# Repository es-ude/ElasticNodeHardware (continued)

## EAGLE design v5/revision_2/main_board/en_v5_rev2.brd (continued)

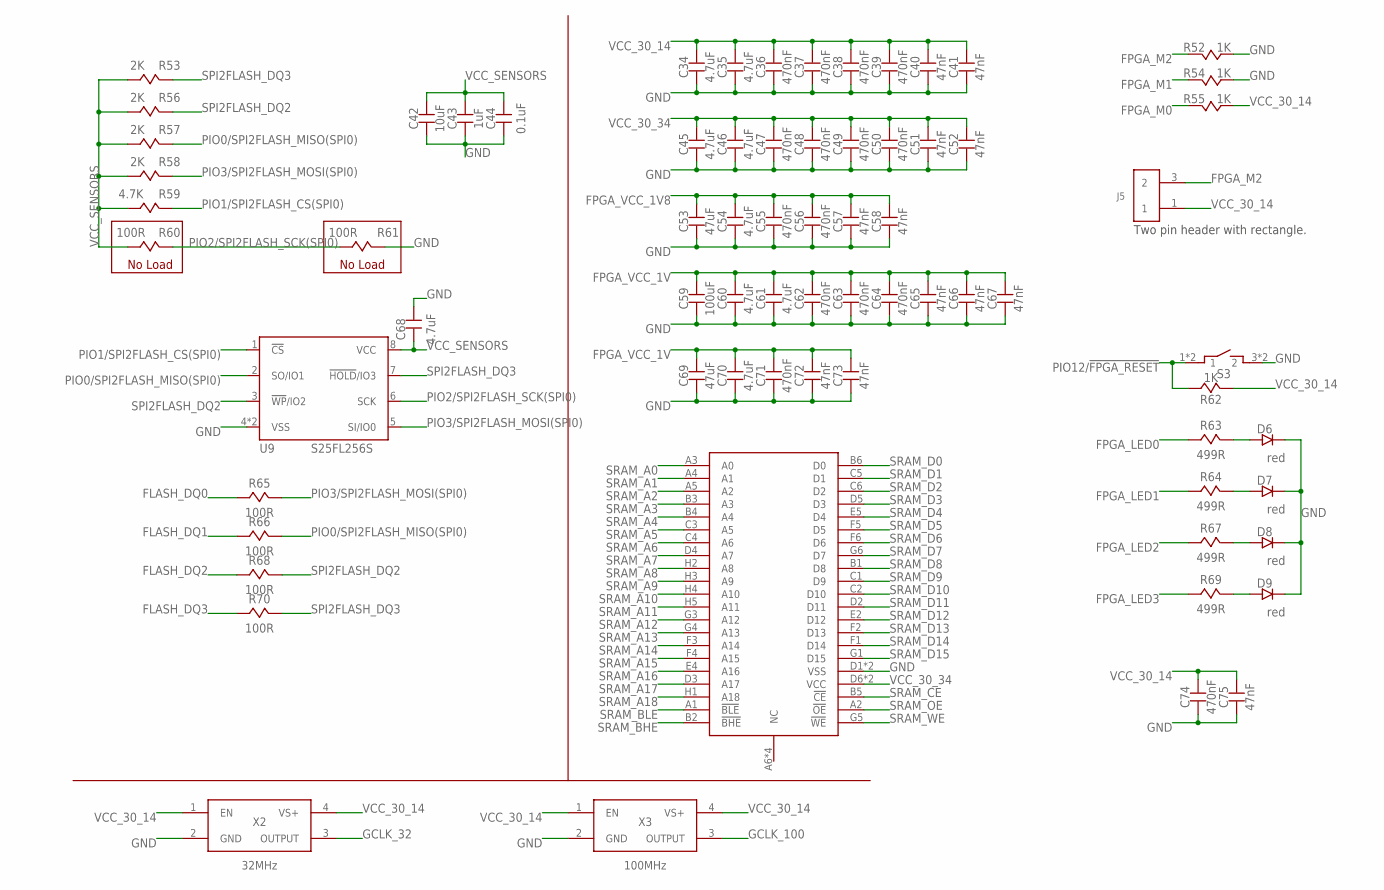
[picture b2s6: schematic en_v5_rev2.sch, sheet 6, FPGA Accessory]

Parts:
C34, C35, C45, C46, C54, C60, C61, C68, C70: 4.7uF; CAPC1608-0603
C36, C37, C38, C39, C47, C48, C49, C50, C55, C56, C62, C63, C64, C71, C74: 470nF; 0402
C40, C41, C51, C52, C57, C58, C65, C66, C67, C72, C73, C75: 47nF; 0402
C42: 10uF; CAPC1608-0603
C43: 1uF; 0402
C44: 0.1uF; 0402
C53, C69: 47uF; 0805
C59: 100uF; 0805
D6, D7, D8, D9: red; 0402
J5: FEMALE_HEADER_2X1; 2X1_HEADER
R52, R54, R55, R62: 1K; 0402
R53, R56, R57, R58: 2K; 0402
R59: 4.7K; 0402
R60, R61, R65, R66, R68, R70: 100R; 0402
R63, R64, R67, R69: 499R; 0402
S3: TACTILE-SWITCH
U9: S25FL256S; WSON6X8MM
U10: CY7C1051DV33; BGA-48
X2: 32MHz; 3.2X2.5_OSC
X3: 100MHz; 3.2X2.5_OSC

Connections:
FLASH_DQ0: R65.1; also elsewhere on the board
FLASH_DQ1: R66.1; also elsewhere on the board
FLASH_DQ2: R68.1; also elsewhere on the board
FLASH_DQ3: R70.1; also elsewhere on the board
FPGA_LED0: R63.1; also elsewhere on the board
FPGA_LED1: R64.1; also elsewhere on the board
FPGA_LED2: R67.1; also elsewhere on the board
FPGA_LED3: R69.1; also elsewhere on the board
FPGA_M0: R55.2; also elsewhere on the board
FPGA_M1: R54.2; also elsewhere on the board
FPGA_M2: J5.3 (2), R52.2; also elsewhere on the board
FPGA_VCC_1V: C59.2, C60.2, C61.2, C62.2, C63.2, C64.2, C65.2, C66.2, C67.2, C69.2, C70.2, C71.2, C72.2, C73.2; also elsewhere on the board
FPGA_VCC_1V8: C53.2, C54.2, C55.2, C56.2, C57.2, C58.2; also elsewhere on the board
GCLK_32: X2.3 (OUTPUT); also elsewhere on the board
GCLK_100: X3.3 (OUTPUT); also elsewhere on the board
GND: C34.1, C35.1, C36.1, C37.1, C38.1, C39.1, C40.1, C41.1, C42.1, C43.1, C44.1, C45.1, C46.1, C47.1, C48.1, C49.1, C50.1, C51.1, C52.1, C53.1, C54.1, C55.1, C56.1, C57.1, C58.1, C59.1, C60.1, C61.1, C62.1, C63.1, C64.1, C65.1, C66.1, C67.1, C68.2, C69.1, C70.1, C71.1, C72.1, C73.1, C74.1, C75.1, D6.2, D7.2, D8.2, D9.2, R52.1, R54.1, R61.2, S3.3 (2), S3.4 (2), U9.4 (VSS), U9.9 (VSS), U10.D1 (VSS), U10.E6 (VSS), X2.2 (GND), X3.2 (GND); also elsewhere on the board
unnamed: D6.1, R63.2
unnamed: D7.1, R64.2
unnamed: D8.1, R67.2
unnamed: D9.1, R69.2
PIO0/SPI2FLASH_MISO(SPI0): R57.2, R66.2, U9.2 (SO/IO1); also elsewhere on the board
PIO1/SPI2FLASH_CS(SPI0): R59.2, U9.1 (!CS); also elsewhere on the board
PIO2/SPI2FLASH_SCK(SPI0): R60.2, R61.1, U9.6 (SCK); also elsewhere on the board
PIO3/SPI2FLASH_MOSI(SPI0): R58.2, R65.2, U9.5 (SI/IO0); also elsewhere on the board
PIO12/!FPGA_RESET: R62.1, S3.1, S3.2 (1); also elsewhere on the board
SPI2FLASH_DQ2: R56.2, R68.2, U9.3 (!WP!/IO2)
SPI2FLASH_DQ3: R53.2, R70.2, U9.7 (!HOLD!/IO3)
SRAM_A0: U10.A3 (A0); also elsewhere on the board
SRAM_A1: U10.A4 (A1); also elsewhere on the board
SRAM_A2: U10.A5 (A2); also elsewhere on the board
SRAM_A3: U10.B3 (A3); also elsewhere on the board
SRAM_A4: U10.B4 (A4); also elsewhere on the board
SRAM_A5: U10.C3 (A5); also elsewhere on the board
SRAM_A6: U10.C4 (A6); also elsewhere on the board
SRAM_A7: U10.D4 (A7); also elsewhere on the board
SRAM_A8: U10.H2 (A8); also elsewhere on the board
SRAM_A9: U10.H3 (A9); also elsewhere on the board
SRAM_A10: U10.H4 (A10); also elsewhere on the board
SRAM_A11: U10.H5 (A11); also elsewhere on the board
SRAM_A12: U10.G3 (A12); also elsewhere on the board
SRAM_A13: U10.G4 (A13); also elsewhere on the board
SRAM_A14: U10.F3 (A14); also elsewhere on the board
SRAM_A15: U10.F4 (A15); also elsewhere on the board
SRAM_A16: U10.E4 (A16); also elsewhere on the board
SRAM_A17: U10.D3 (A17); also elsewhere on the board
SRAM_A18: U10.H1 (A18); also elsewhere on the board
SRAM_BHE: U10.B2 (!BHE); also elsewhere on the board
SRAM_BLE: U10.A1 (!BLE); also elsewhere on the board
SRAM_CE: U10.B5 (!CE); also elsewhere on the board
SRAM_D0: U10.B6 (D0); also elsewhere on the board
SRAM_D1: U10.C5 (D1); also elsewhere on the board
SRAM_D2: U10.C6 (D2); also elsewhere on the board
SRAM_D3: U10.D5 (D3); also elsewhere on the board
SRAM_D4: U10.E5 (D4); also elsewhere on the board
SRAM_D5: U10.F5 (D5); also elsewhere on the board
SRAM_D6: U10.F6 (D6); also elsewhere on the board
SRAM_D7: U10.G6 (D7); also elsewhere on the board
SRAM_D8: U10.B1 (D8); also elsewhere on the board
SRAM_D9: U10.C1 (D9); also elsewhere on the board
SRAM_D10: U10.C2 (D10); also elsewhere on the board
SRAM_D11: U10.D2 (D11); also elsewhere on the board
SRAM_D12: U10.E2 (D12); also elsewhere on the board
SRAM_D13: U10.F2 (D13); also elsewhere on the board
SRAM_D14: U10.F1 (D14); also elsewhere on the board
SRAM_D15: U10.G1 (D15); also elsewhere on the board
SRAM_OE: U10.A2 (!OE); also elsewhere on the board
SRAM_WE: U10.G5 (!WE); also elsewhere on the board
VCC_30_14: C34.2, C35.2, C36.2, C37.2, C38.2, C39.2, C40.2, C41.2, C74.2, C75.2, J5.1, R55.1, R62.2, X2.1 (EN), X2.4 (VS+), X3.1 (EN), X3.4 (VS+); also elsewhere on the board
VCC_30_34: C45.2, C46.2, C47.2, C48.2, C49.2, C50.2, C51.2, C52.2, U10.D6 (VCC), U10.E1 (VCC); also elsewhere on the board
VCC_SENSORS: C42.2, C43.2, C44.2, C68.1, R53.1, R56.1, R57.1, R58.1, R59.1, R60.1, U9.8 (VCC); also elsewhere on the board

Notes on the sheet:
No Load
Two pin header with rectangle.

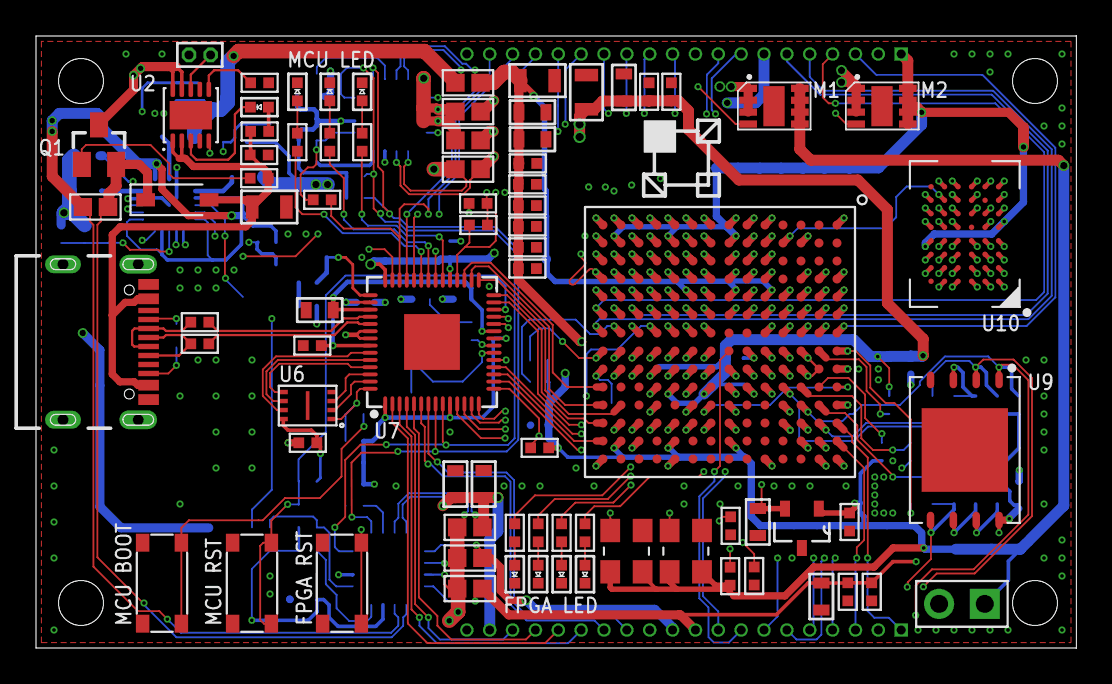
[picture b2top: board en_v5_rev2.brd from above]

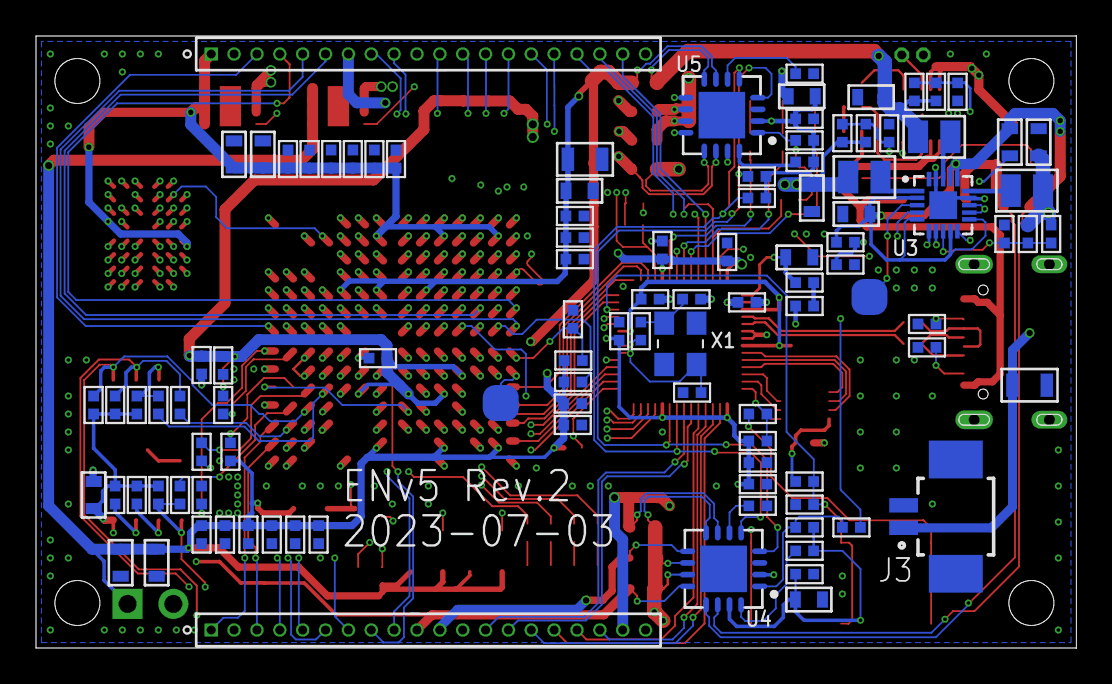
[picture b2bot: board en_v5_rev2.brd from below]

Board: 4 copper layers, 57.8 x 34.0 mm, 183 parts (104 on the bottom side), 170 nets.

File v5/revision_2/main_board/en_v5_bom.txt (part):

Qty Value                   Device                     Package                   Parts                                                                     Description                                                                                                                           
14  0.1uF                   CAPACITOR0402              0402                      C3, C14, C16, C18, C19, C20, C21, C22, C23, C24, C26, C27, C30, C44                                                                                                                                             
2   0.1uF                   CAPACITOR0603              CAPC1608-0603             C5, C6                                                                                                                                                                                                          
1   0.1uF                   CAPACITOR0805              0805                      C1                                                                                                                                                                                                              
8   0.82R                   RESISTOR0603               0603                      R16, R17, R18, R19, R20, R21, R26, R28                                                                                                                                                                          
7   0R                      RESISTORSMD_0402           0402                      R4, R10, R27, R29, R47, R48, R49                                                                                                                                                                                
1   1.5uH(MLP2016H1R5MT0S1) INDUCTORDFE201612E-R33M=P2 INDC2016X120N             L1                                                                                                                                                                                                              
1   100MHz                  OSCILLATOR3.2X2.5          3.2X2.5_OSC               X3                                                                                                                                                                                                              
7   100R                    RESISTORSMD_0402           0402                      R33, R60, R61, R65, R66, R68, R70                                                                                                                                                                               
1   100uF                   CAPACITOR0805              0805                      C59                                                                                                                                                                                                             
7   10K                     RESISTORSMD_0402           0402                      R3, R22, R23, R24, R25, R34, R44                                                                                                                                                                                
5   10uF                    CAPACITOR0603              CAPC1608-0603             C4, C8, C10, C12, C42                                                                                                                                                                                           
1   10uF                    CAPACITOR0805              0805                      C2                                                                                                                                                                                                              
3   120K                    RESISTORSMD_0402           0402                      R9, R12, R13                                                                                                                                                                                                    
1   12MHz                   QUARTZ                     3.2X2.5_OSC               X1                                                                                                                                                                                                              
1   150K                    RESISTORSMD_0402           0402                      R11                                                                                                                                                                                                             
1   180K                    RESISTORSMD_0402           0402                      R14                                                                                                                                                                                                             
7   1K                      RESISTORSMD_0402           0402                      R6, R46, R51, R52, R54, R55, R62                                                                                                                                                                                
1   1R                      RESISTORSMD_0402           0402                      R41                                                                                                                                                                                                             
2   1uF                     CAPACITOR0402              0402                      C33, C43                                                                                                                                                                                                        
1   2.2uH(MLP2016H2R2MT0S1) INDUCTORDFE201612E-R33M=P2 INDC2016X120N             L3                                                                                                                                                                                                              
1   2.7pF                   CAPACITOR0402              0402                      C11                                                                                                                                                                                                             
1   200R                    RESISTORSMD_0402           0402                      R37                                                                                                                                                                                                             
2   20pF                    CAPACITOR0402              0402                      C31, C32                                                                                                                                                                                                        
2   27R                     RESISTORSMD_0402           0402                      R42, R43                                                                                                                                                                                                        
7   2K                      RESISTORSMD_0402           0402                      R5, R45, R50, R53, R56, R57, R58                                                                                                                                                                                
1   3.3pF                   CAPACITOR0402              0402                      C9                                                                                                                                                                                                              
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
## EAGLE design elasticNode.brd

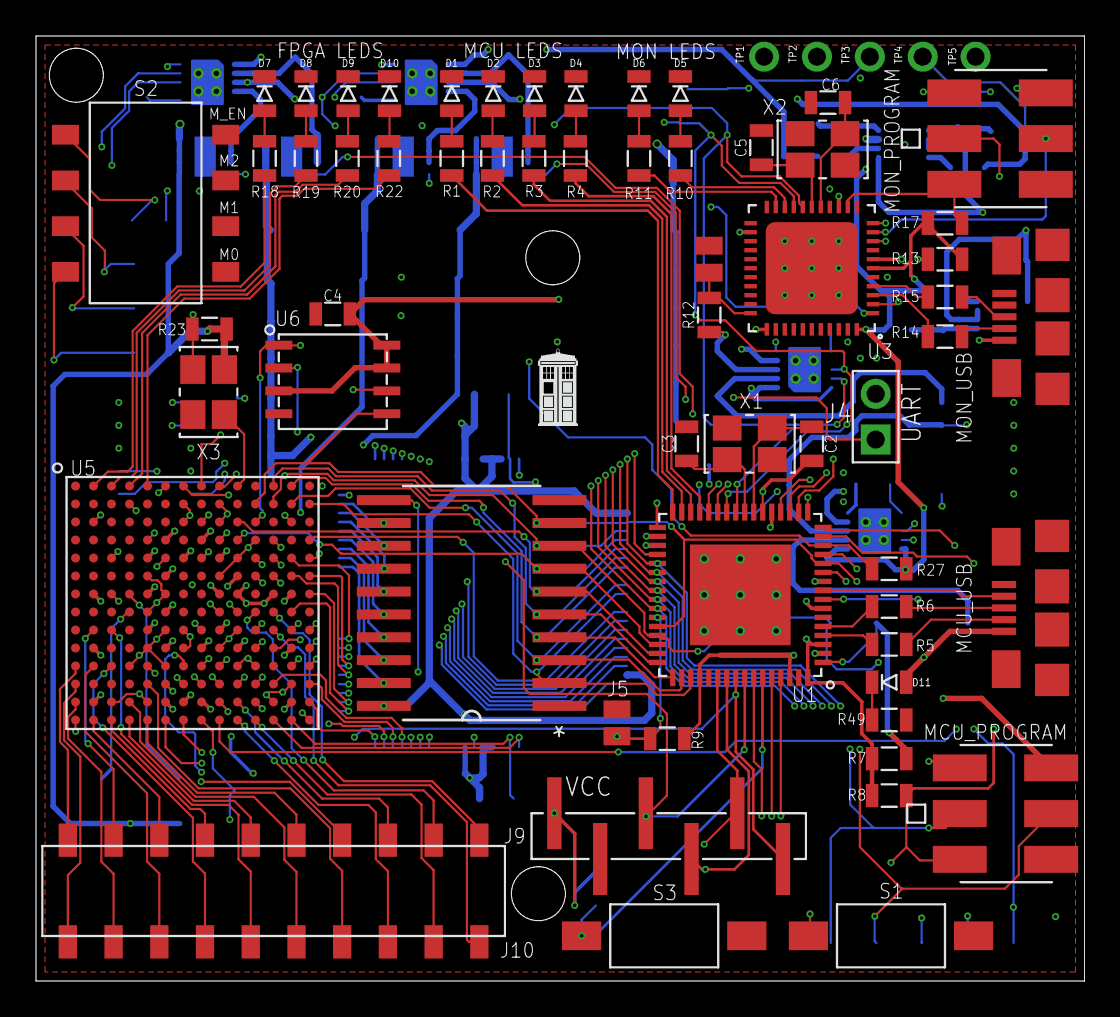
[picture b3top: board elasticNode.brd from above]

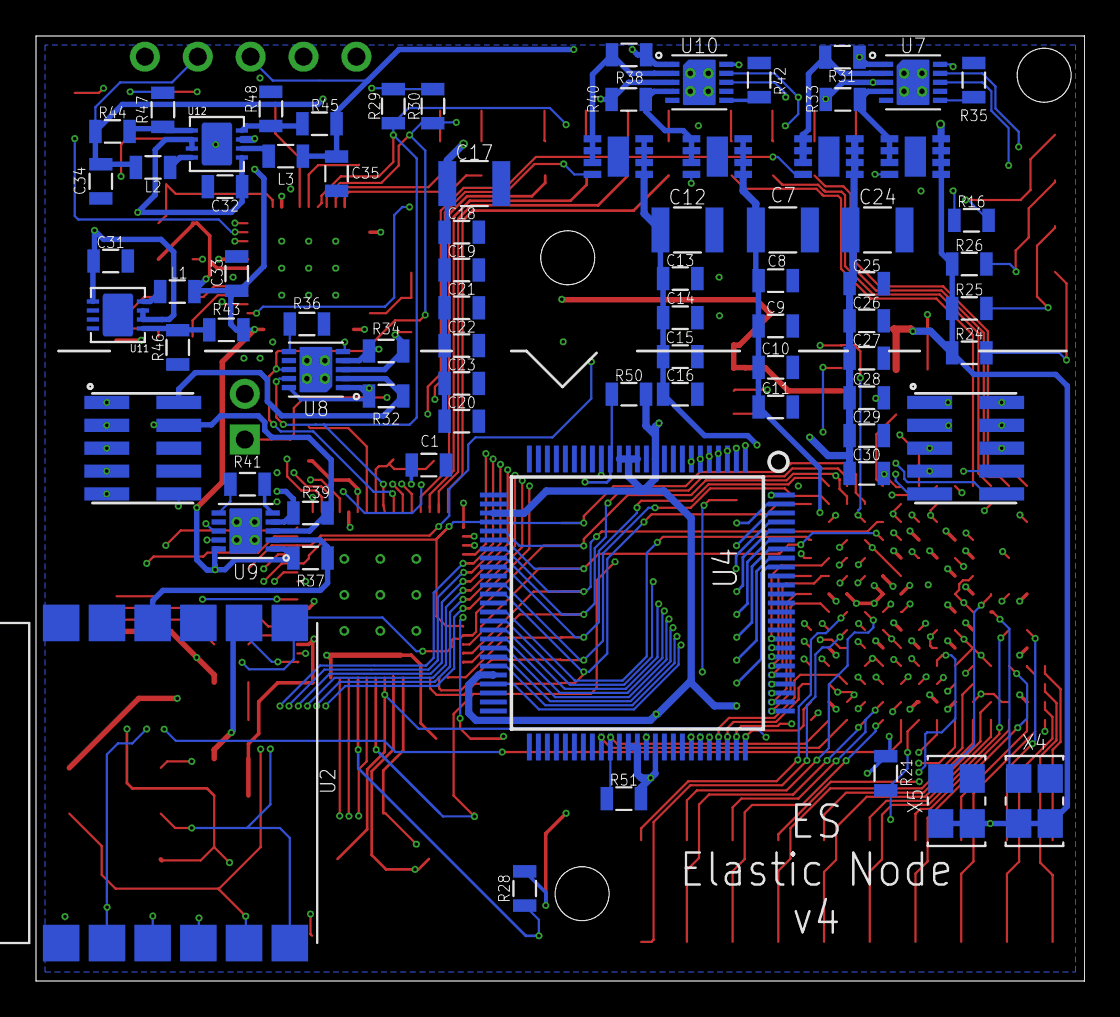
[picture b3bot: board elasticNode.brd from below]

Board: 4 copper layers, 58.2 x 52.5 mm, 141 parts (77 on the bottom side), 171 nets.

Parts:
C1, C4, C31, C32: 10u; 0805
C2, C3, C5, C6: 20p; 0805
C7, C17, C24: 100u; 1210
C8, C9, C13, C18, C19, C20, C25, C26, C27: 4.7u; 0805
C10, C11, C14, C15, C16, C21, C22, C23, C28, C29, C30: 0.47u; 0805
C12: 47u; 1210
C33, C34, C35: 22u; 0805
D1, D2, D3, D4, D5, D6: GREEN 2.2V; 0805
D7: RED 1.8V 2mA; 0805
D8, D9, D10, D11: RED; 0805
J1, J2: FEMALE_HEADER_5X2; 5X2_HEADER_SMT_1.27
J3, J6: ISP_CONN_6PIN; ICSP_SMT
J4: FEMALE_HEADER_2X1; 2X1_HEADER
J5, J7: JUMPER; JUMPER_SMT
J8, J11: USB_CONNMICRO_SMT; USB_MICRO_B_SMT
J9: JTAG_CONN_6PINSMT; 6X1_JTAG
J10: FEMALE_HEADER_10X2; 10X2_HEADER_SMT
L1, L2, L3: 3.3uH; 0805
M1, M2, M3, M4: SISS23DN; POWERPAK1212-8
R1, R2, R3, R4, R10, R11: 550; 0805
R5, R6, R14, R15: 22; 0805
R7, R16, R24, R25, R26, R27: 2.4k; 0805
R8, R12, R17, R23, R28, R47: 15k; 0805
R9, R44, R48, R50, R51: 10k; 0805
R13: 0; 0805
R18, R19, R20, R22, R41: 750; 0805
R21: 4.7k; 0805
R29, R30: 1.5k; 0805
R31, R33: 0.8; 0805
R32, R34, R37, R38, R40: .8; 0805
R35: 100; 0805
R36: 2000; 0805
R39: 0.15; 0805
R42: 300; 0805
R43: 6k8; 0805
R45: 20k; 0805
R46: 1k5; 0805
R49: 270; 0805
S1, S3: SPST_BUTTON2PIN_SMT; SPST_2PIN_SMT
S2: SPST_DIP_4; SPST_DIP4_SMT
TP1, TP2, TP3, TP4, TP5: TEST_POINTTHT; THT
U1: AT90USB128; QFN64
U2: MRF24J40MA
U3: ATMEGA32U4QFN; QFN44
U4: IDT7028L15-TQFP100; TQFP100
U5: SPARTAN7-LX15; FTGB196
U6: SST26VF032BWDFN; WDFN8
U7, U8, U9, U10: PAC1720; VDFN10
U11, U12: LTC3419DFN; DFN8
U13: 74AHC573; SOIC20
X1, X2: 8MHz; 3.2X2.5_OSC
X3: 100MHz; 3.2X2.5_OSC
X4: 50MHz; 3.2X2.5_OSC
X5: 32MHz; 3.2X2.5_OSC

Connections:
1V: C34.1, L2.2, R40.2, R44.2, TP4.3, U10.3
1V8: C35.2, L3.1, R31.2, R38.2, R45.1, TP3.3, U7.1, U10.1
3V3: C4.1, C33.1, J3.2, J6.2, L1.1, R12.1, R13.2, R16.1, R17.1, R27.1, R29.2, R30.2, R32.2, R33.2, R34.2, R37.2, R43.2, TP2.3, U3.6, U3.14, U3.24, U3.34, U3.44, U6.3, U6.7, U6.8, U7.3, U7.10, U8.1, U8.3, U8.10, U9.1, U9.10, U10.10, U12.7
5V: C31.1, C32.1, J2.9, R39.2, TP1.3, U9.3, U11.2, U11.3, U11.5, U12.2, U12.3, U12.5
DAUGHTER_VCC: J2.10, R32.1, U8.2
EN_OSC_100: R23.1, U1.17, X3.1
FPGA_AUX_POWER: M2.4, U1.18
FPGA_DONE: U1.16, U5.P9
FPGA_GPIO_1: J10.1, U5.J12
FPGA_GPIO_2: J10.2, U5.P11
FPGA_GPIO_3: J10.3, U5.P10
FPGA_GPIO_4: J10.4, U5.M5
FPGA_GPIO_5: J10.5, U5.N4
FPGA_GPIO_6: J10.6, U5.J3
FPGA_GPIO_7: J10.7, U5.L3
FPGA_GPIO_8: J10.8, U5.L2
FPGA_GPIO_9: J10.9, U5.N1
FPGA_GPIO_10: J10.10, U5.M1
FPGA_GPIO_11: J10.11, U5.L1
FPGA_GPIO_12: J10.12, U5.J2
FPGA_GPIO_13: J10.13, U5.P2
FPGA_GPIO_14: J10.14, U5.P3
FPGA_GPIO_15: J10.15, U5.P4
FPGA_GPIO_16: J10.16, U5.P5
FPGA_GPIO_17: J10.17, U5.L5
FPGA_GPIO_18: J10.18, U5.N10
FPGA_GPIO_19: J10.19, U5.H11
FPGA_GPIO_20: J10.20, U5.H12
FPGA_INT_POWER: M1.4, U1.10
FPGA_IO_POWER: M3.4, U1.2
FPGA_LED0: R18.1, U5.A2
FPGA_LED1: R19.1, U5.A3
FPGA_LED2: R20.1, U5.A4
FPGA_LED3: R22.1, U5.A5
FPGA_RESET: R28.1, S3.2, U1.59, U5.L7
FPGA_VCCAUX: C12.1, C13.1, C14.1, C15.1, C16.1, M2.5, M2.6, M2.7, M2.8, U5.F10, U5.H10, U5.K10, U5.L9, U5.N7
FPGA_VCCAUX_MON: M2.1, M2.2, M2.3, R38.1, U10.2
FPGA_VCCINT: C7.1, C8.1, C9.1, C10.1, C11.1, M1.5, M1.6, M1.7, M1.8, U5.D6, U5.D8, U5.E5, U5.E7, U5.E9, U5.F6, U5.G5, U5.G9, U5.H6, U5.J5, U5.J9, U5.K6, U5.K8
FPGA_VCCINT_MON: M1.1, M1.2, M1.3, R40.1, U10.4
FPGA_VCCIO: C17.1, C18.1, C19.1, C20.1, C21.1, C22.1, C23.1, J9.1, M3.5, M3.6, M3.7, M3.8, R21.2, R23.2, R24.1, R25.1, R26.1, R28.2, U5.G2, U5.G13, U5.K2, U5.K13, U5.N2, U5.N6, U5.N8, U5.N13, X3.4, X4.1, X4.4, X5.1, X5.4
FPGA_VCCIO_MON: M3.1, M3.2, M3.3, R33.1, U7.4
GND: C1.2, C2.2, C3.2, C4.2, C5.2, C6.2, C7.2, C8.2, C9.2, C10.2, C11.2, C12.2, C13.2, C14.2, C15.2, C16.2, C17.2, C18.2, C19.2, C20.2, C21.2, C22.2, C23.2, C24.2, C25.2, C26.2, C27.2, C28.2, C29.2, C30.2, C31.2, C32.2, C33.2, C34.2, C35.1, D1.2, D2.2, D3.2, D4.2, D5.2, D6.2, D7.2, D8.2, D9.2, D10.2, J2.7, J2.8, J3.6, J5.2, J6.6, J7.2, J8.5, J9.2, J11.5, R35.1, R36.1, R41.1, R42.1, R46.2, R47.2, R48.1, R49.1, S1.1, S2.5, S2.6, S2.7, S2.8, S3.1, TP5.3, U1.6, U1.22, U1.53, U1.63, U1.PAD, U1.VIA1, U1.VIA2, U1.VIA3, U1.VIA4, U1.VIA5, U1.VIA6, U1.VIA7, U1.VIA8, U1.VIA9, U2.1, U2.11, U2.12, U3.5, U3.15, U3.23, U3.35, U3.43, U3.45, U4.10, U4.12, U4.18, U4.19, U4.35, U4.38, U4.57, U4.58, U4.61, U4.64, U4.66, U4.87, U4.88, U5.A1, U5.A6, U5.A9, U5.A11, U5.A14, U5.B4, U5.B7, U5.B9, U5.C2, U5.C6, U5.C7, U5.C8, U5.C9, U5.C13, U5.D5, U5.D7, U5.D9, U5.D11, U5.E1, U5.E3, U5.E6, U5.E8, U5.E10, U5.E14, U5.F5, U5.F9, U5.G3, U5.G6, U5.G10, U5.G12, U5.H5, U5.H9, U5.J6, U5.J7, U5.J8, U5.J10, U5.K1, U5.K5, U5.K7, U5.K9, U5.K14, U5.L4, U5.L6, U5.L8, U5.L10, U5.L11, U5.L12, U5.M13, U5.N3, U5.N5, U5.N9, U5.N12, U5.P1, U5.P14, U6.4, U7.5, U7.P$1, U7.P$2, U7.P$3, U7.P$4, U8.5, U8.P$1, U8.P$2, U8.P$3, U8.P$4, U9.5, U9.P$1, U9.P$2, U9.P$3, U9.P$4, U10.5, U10.P$1, U10.P$2, U10.P$3, U10.P$4, U11.9, U12.9, U13.1, U13.10, X3.2, X4.2, X5.2
INIT_B: R21.1, U1.58, U5.P8
JTAG_TCK: J9.3, U1.57, U5.A7
JTAG_TDI: J9.5, U1.54, U5.P7
JTAG_TDO: J9.4, U1.55, U5.P6
JTAG_TMS: J9.6, U1.56, U5.M6
MCU_LED0: R1.1, U1.32
MCU_LED1: R2.1, U1.31
MCU_LED2: R3.1, U1.30
MCU_LED3: R4.1, U1.29
MCU_RESET: J3.5, R8.1, S1.2, U1.20
MCU_RX: J4.3, U1.27
MCU_TX: J4.1, U1.28
MCU_VCC: C1.1, R7.1, R8.2, R9.1, R34.1, U1.3, U1.7, U1.21, U1.52, U1.62, U1.64, U8.4
MODE0: R24.2, S2.1, U5.M7
MODE1: R25.2, S2.2, U5.M8
MODE2: R26.2, S2.3, U5.M9
MONITORING: R16.2, S2.4, U3.1
MON_HWB: J7.1, R12.2, U3.33
MON_LED0: R10.1, U3.20
MON_LED1: R11.1, U3.21
MON_MISO: J6.1, U3.11
MON_MOSI: J6.4, U3.10
MON_RESET: J6.5, R17.2, U3.13
MON_SCK: J6.3, U3.9
MON_USB_D+: R15.1, U3.4
MON_USB_D-: R14.1, U3.3
MON_USB_VCC: J8.1, U3.7
unnamed: R44.1, R47.1, U12.1
unnamed: R5.2, U1.4
unnamed: C2.1, U1.23, X1.1
unnamed: J8.3, R15.2
unnamed: C3.1, U1.24, X1.3
unnamed: R45.2, R48.2, U12.8
unnamed: R42.2, U10.6
unnamed: R6.2, U1.5
unnamed: R41.2, U9.6
unnamed: R35.2, U7.6
unnamed: D4.1, R4.2
unnamed: R36.2, U8.6
unnamed: D3.1, R3.2
unnamed: D6.1, R11.2
unnamed: D5.1, R10.2
unnamed: C5.1, U3.17, X2.3
unnamed: J8.2, R14.2
unnamed: C6.1, U3.16, X2.1
unnamed: R13.1, U3.2
unnamed: L2.1, U12.4
unnamed: D2.1, R2.2
unnamed: D1.1, R1.2
unnamed: D10.1, R22.2
unnamed: L3.2, U12.6
unnamed: D9.1, R20.2
unnamed: D11.2, R49.2
unnamed: D8.1, R19.2
unnamed: D7.1, R18.2
unnamed: R43.1, R46.1, U11.1
unnamed: L1.2, U11.4
OSC_32: U5.G4, X5.3
OSC_50: U5.H4, X4.3
OSC_100: U5.A10, X3.3
SCL: J1.1, R29.1, U1.25, U3.18, U7.9, U8.9, U9.9, U10.9
SDA: J1.2, R30.1, U1.26, U3.19, U7.8, U8.8, U9.8, U10.8
SELECTMAP_D0/SPI_MOSI/PDI/XMEGA_AD7: J1.5, J3.4, U1.12, U1.44, U2.5, U4.29, U5.B11, U6.5, U13.9
SELECTMAP_D1/SPI_MISO/MCU_PDO/XMEGA_AD6: J1.6, J3.1, U1.13, U1.45, U2.7, U4.30, U5.B12, U6.2, U13.8
SELECTMAP_D2/FPGA_WP/XMEGA_AD5: J1.4, U1.46, U4.31, U5.D10, U13.7
SELECTMAP_D3/FPGA_HOLD/XMEGA_AD4: J1.7, U1.47, U4.32, U5.C10, U13.6
SELECTMAP_D4/MCU_TX1/XMEGA_AD3: J1.3, U1.48, U4.33, U5.A12, U13.5
SELECTMAP_D5/MCU_RX1/XMEGA_AD2: J1.8, U1.49, U4.34, U5.A13, U13.4
SELECTMAP_D6/XMEGA_AD1: U1.50, U4.36, U5.B13, U13.3
SELECTMAP_D7/XMEGA_AD0: U1.51, U4.37, U5.B14, U13.2
SPI_CS: R27.2, U1.14, U5.C11, U6.1
SPI_SCK/CCLK: J3.3, U1.11, U2.6, U5.A8, U6.6
SRAM_POWER: M4.4, U1.19
SRAM_VDD: C24.1, C25.1, C26.1, C27.1, C28.1, C29.1, C30.1, M4.5, M4.6, M4.7, M4.8, R50.2, R51.2, U4.11, U4.13, U4.14, U4.15, U4.28, U4.46, U4.62, U4.63, U4.65, U13.20
SRAM_VDD_MON: M4.1, M4.2, M4.3, R31.1, U7.2
UID: J11.4, U1.9
USBD+: J11.3, R6.1
USBD-: J11.2, R5.1
USB_VCC_RAW: D11.1, J11.1, R39.1, U1.8, U9.4
WIRELESS_CS: R7.2, U1.1, U2.8
WIRELESS_INT: U1.61, U2.4
WIRELESS_RESET: U1.15, U2.2
WIRELESS_VCC: R37.1, U2.10, U9.2
WIRELESS_WAKE: U1.60, U2.3
XFPGA_A0: U4.84, U5.E13
XFPGA_A1: U4.83, U5.E12
XFPGA_A2: U4.82, U5.E11
XFPGA_A3: U4.81, U5.F14
XFPGA_A4: U4.80, U5.F13
XFPGA_A5: U4.79, U5.F12
XFPGA_A6: U4.78, U5.F11
XFPGA_A7: U4.77, U5.G14
XFPGA_A8: U4.76, U5.H13
XFPGA_A9: U4.75, U5.N14
XFPGA_A10: U4.74, U5.N11
XFPGA_A11: U4.73, U5.M14
XFPGA_A12: U4.72, U5.M12
XFPGA_A13: U4.71, U5.M11
XFPGA_A14: U4.70, U5.M10
XFPGA_A15: U4.69, U5.L14
XFPGA_D0: U4.39, U5.D14
XFPGA_D1: U4.40, U5.D12
XFPGA_D2: U4.41, U5.J11
XFPGA_D3: U4.42, U5.K11
XFPGA_D4: U4.43, U5.J13
XFPGA_D5: U4.44, U5.J14
XFPGA_D6: U4.45, U5.K12
XFPGA_D7: U4.47, U5.L13
XFPGA_RD: U4.59, U5.P12
XFPGA_WR: R51.1, U4.60, U5.P13
XMEGA_A0: U4.92, U13.19
XMEGA_A1: U4.93, U13.18
XMEGA_A2: U4.94, U13.17
XMEGA_A3: U4.95, U13.16
XMEGA_A4: U4.96, U13.15
XMEGA_A5: U4.97, U13.14
XMEGA_A6: U4.98, U13.13
XMEGA_A7: U4.99, U13.12
XMEGA_A8: J1.9, U1.35, U4.100
XMEGA_A9: U1.36, U4.1
XMEGA_A10: J2.6, U1.37, U4.2
XMEGA_A11: J2.5, U1.38, U4.3
XMEGA_A12: J2.4, U1.39, U4.4
XMEGA_A13: J2.3, U1.40, U4.5
XMEGA_A14: J2.2, U1.41, U4.6
XMEGA_A15: J2.1, U1.42, U4.7
XMEGA_RD: J1.10, U1.34, U4.17
XMEGA_WR: R50.1, U1.33, U4.16
XMEM_ALE/HWB: J5.1, R9.2, U1.43, U13.11

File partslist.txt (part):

Partlist exported from /Users/superchange/Documents/gits/elasticnodehardware/elasticNode.sch at 2019/3/26 16:11

Part Value               Device              Package             Description SPICEPREFIX
C1   10u                 CAPACITOR0805       0805                                       
C2   20p                 CAPACITOR0805       0805                                       
C3   20p                 CAPACITOR0805       0805                                       
C4   10u                 CAPACITOR0805       0805                                       
C5   20p                 CAPACITOR0805       0805                                       
C6   20p                 CAPACITOR0805       0805                                       
C7   100u                CAPACITOR1210       1210                                       
C8   4.7u                CAPACITOR1210       1210                                       
C9   4.7u                CAPACITOR0805       0805                                       
C10  0.47u               CAPACITOR0805       0805                                       
C11  0.47u               CAPACITOR0805       0805                                       
C12  47u                 CAPACITOR1210       1210                                       
C13  4.7                 CAPACITOR0805       0805                                       
C14  0.47u               CAPACITOR0805       0805                                       
C15  0.47u               CAPACITOR0805       0805                                       
C16  0.47u               CAPACITOR0805       0805                                       
C17  100u                CAPACITOR1210       1210                                       
C18  4.7u                CAPACITOR0805       0805                                       
C19  4.7u                CAPACITOR0805       0805                                       
C20  4.7u                CAPACITOR0805       0805                                       
C21  0.47u               CAPACITOR0805       0805                                       
C22  0.47u               CAPACITOR0805       0805                                       
C23  0.47u               CAPACITOR0805       0805                                       
C24  100u                CAPACITOR1210       1210                                       
C25  4.7u                CAPACITOR0805       0805                                       
C26  4.7u                CAPACITOR0805       0805                                       
C27  4.7u                CAPACITOR0805       0805                                       
C28  0.47u               CAPACITOR0805       0805                                       
C29  0.47u               CAPACITOR0805       0805                                       
C30  0.47u               CAPACITOR0805       0805                                       
C31  10u                 CAPACITOR0805       0805                                       
C32  10u                 CAPACITOR0805       0805                                       
C33  22u                 CAPACITOR0805       0805                                       
C34  22u                 CAPACITOR0805       0805                                       
C35  22u                 CAPACITOR0805       0805                                       
D1   GREEN 2.2V          LED                 0805                                       
D2   GREEN 2.2V          LED                 0805                                       
D3   GREEN 2.2V          LED                 0805                                       
D4   GREEN 2.2V          LED                 0805                                       
D5   GREEN 2.2V          LED                 0805                                       
D6   GREEN 2.2V          LED                 0805                                       
D7   RED 1.8V 2mA        LED                 0805                                       
D8   RED                 LED                 0805                                       
D9   RED                 LED                 0805                                       
D10  RED                 LED                 0805                                       
D11  RED                 LED                 0805                                       
J1   FEMALE_HEADER_5X2   FEMALE_HEADER_5X2   5X2_HEADER_SMT_1.27                        
J2   FEMALE_HEADER_5X2   FEMALE_HEADER_5X2   5X2_HEADER_SMT_1.27                        
J3   ISP_CONN_6PIN       ISP_CONN_6PIN       ICSP_SMT                        X          
J4   FEMALE_HEADER_2X1   FEMALE_HEADER_2X1   2X1_HEADER                                 
J5   JUMPER              JUMPER              JUMPER_SMT                                 
J6   ISP_CONN_6PIN       ISP_CONN_6PIN       ICSP_SMT                                   
J7   JUMPER              JUMPER              JUMPER_SMT                                 
J8   USB_CONNMICRO_SMT   USB_CONNMICRO_SMT   USB_MICRO_B_SMT                            
J9   JTAG_CONN_6PINSMT   JTAG_CONN_6PINSMT   6X1_JTAG                                   
J10  FEMALE_HEADER_10X2  FEMALE_HEADER_10X2  10X2_HEADER_SMT                            
J11  USB_CONNMICRO_SMT   USB_CONNMICRO_SMT   USB_MICRO_B_SMT                            
L1   3.3uH               INDUCTOR            0805                                       
L2   3.3uH               INDUCTOR            0805                                       
L3   3.3uH               INDUCTOR            0805                                       
M1   SISS23DN            SISS23DN            POWERPAK1212-8                             
M2   SISS23DN            SISS23DN            POWERPAK1212-8                             
M3   SISS23DN            SISS23DN            POWERPAK1212-8                             
M4   SISS23DN            SISS23DN            POWERPAK1212-8                             
R1   550                 RESISTOR            0805                                       
R2   550                 RESISTOR            0805                                       
R3   550                 RESISTOR            0805                                       
R4   550                 RESISTOR            0805                                       
R5   22                  RESISTOR            0805                                       
R6   22                  RESISTOR            0805                                       
R7   2.4k                RESISTOR            0805                                       
R8   15k                 RESISTOR            0805                                       
R9   10k                 RESISTOR            0805                                       
R10  550                 RESISTOR            0805                                       
R11  550                 RESISTOR            0805                                       
R12  15k                 RESISTOR            0805                                       
R13  0                   RESISTOR            0805                                       
R14  22                  RESISTOR            0805                                       
R15  22                  RESISTOR            0805                                       
R16  2.4k                RESISTOR            0805                                       
R17  15k                 RESISTOR            0805                                       
R18  750                 RESISTOR            0805                                       
R19  750                 RESISTOR            0805                                       
R20  750                 RESISTOR            0805                                       
R21  4.7k                RESISTOR            0805                                       
R22  750                 RESISTOR            0805                                       
R23  2.4k                RESISTOR            0805                                       
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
